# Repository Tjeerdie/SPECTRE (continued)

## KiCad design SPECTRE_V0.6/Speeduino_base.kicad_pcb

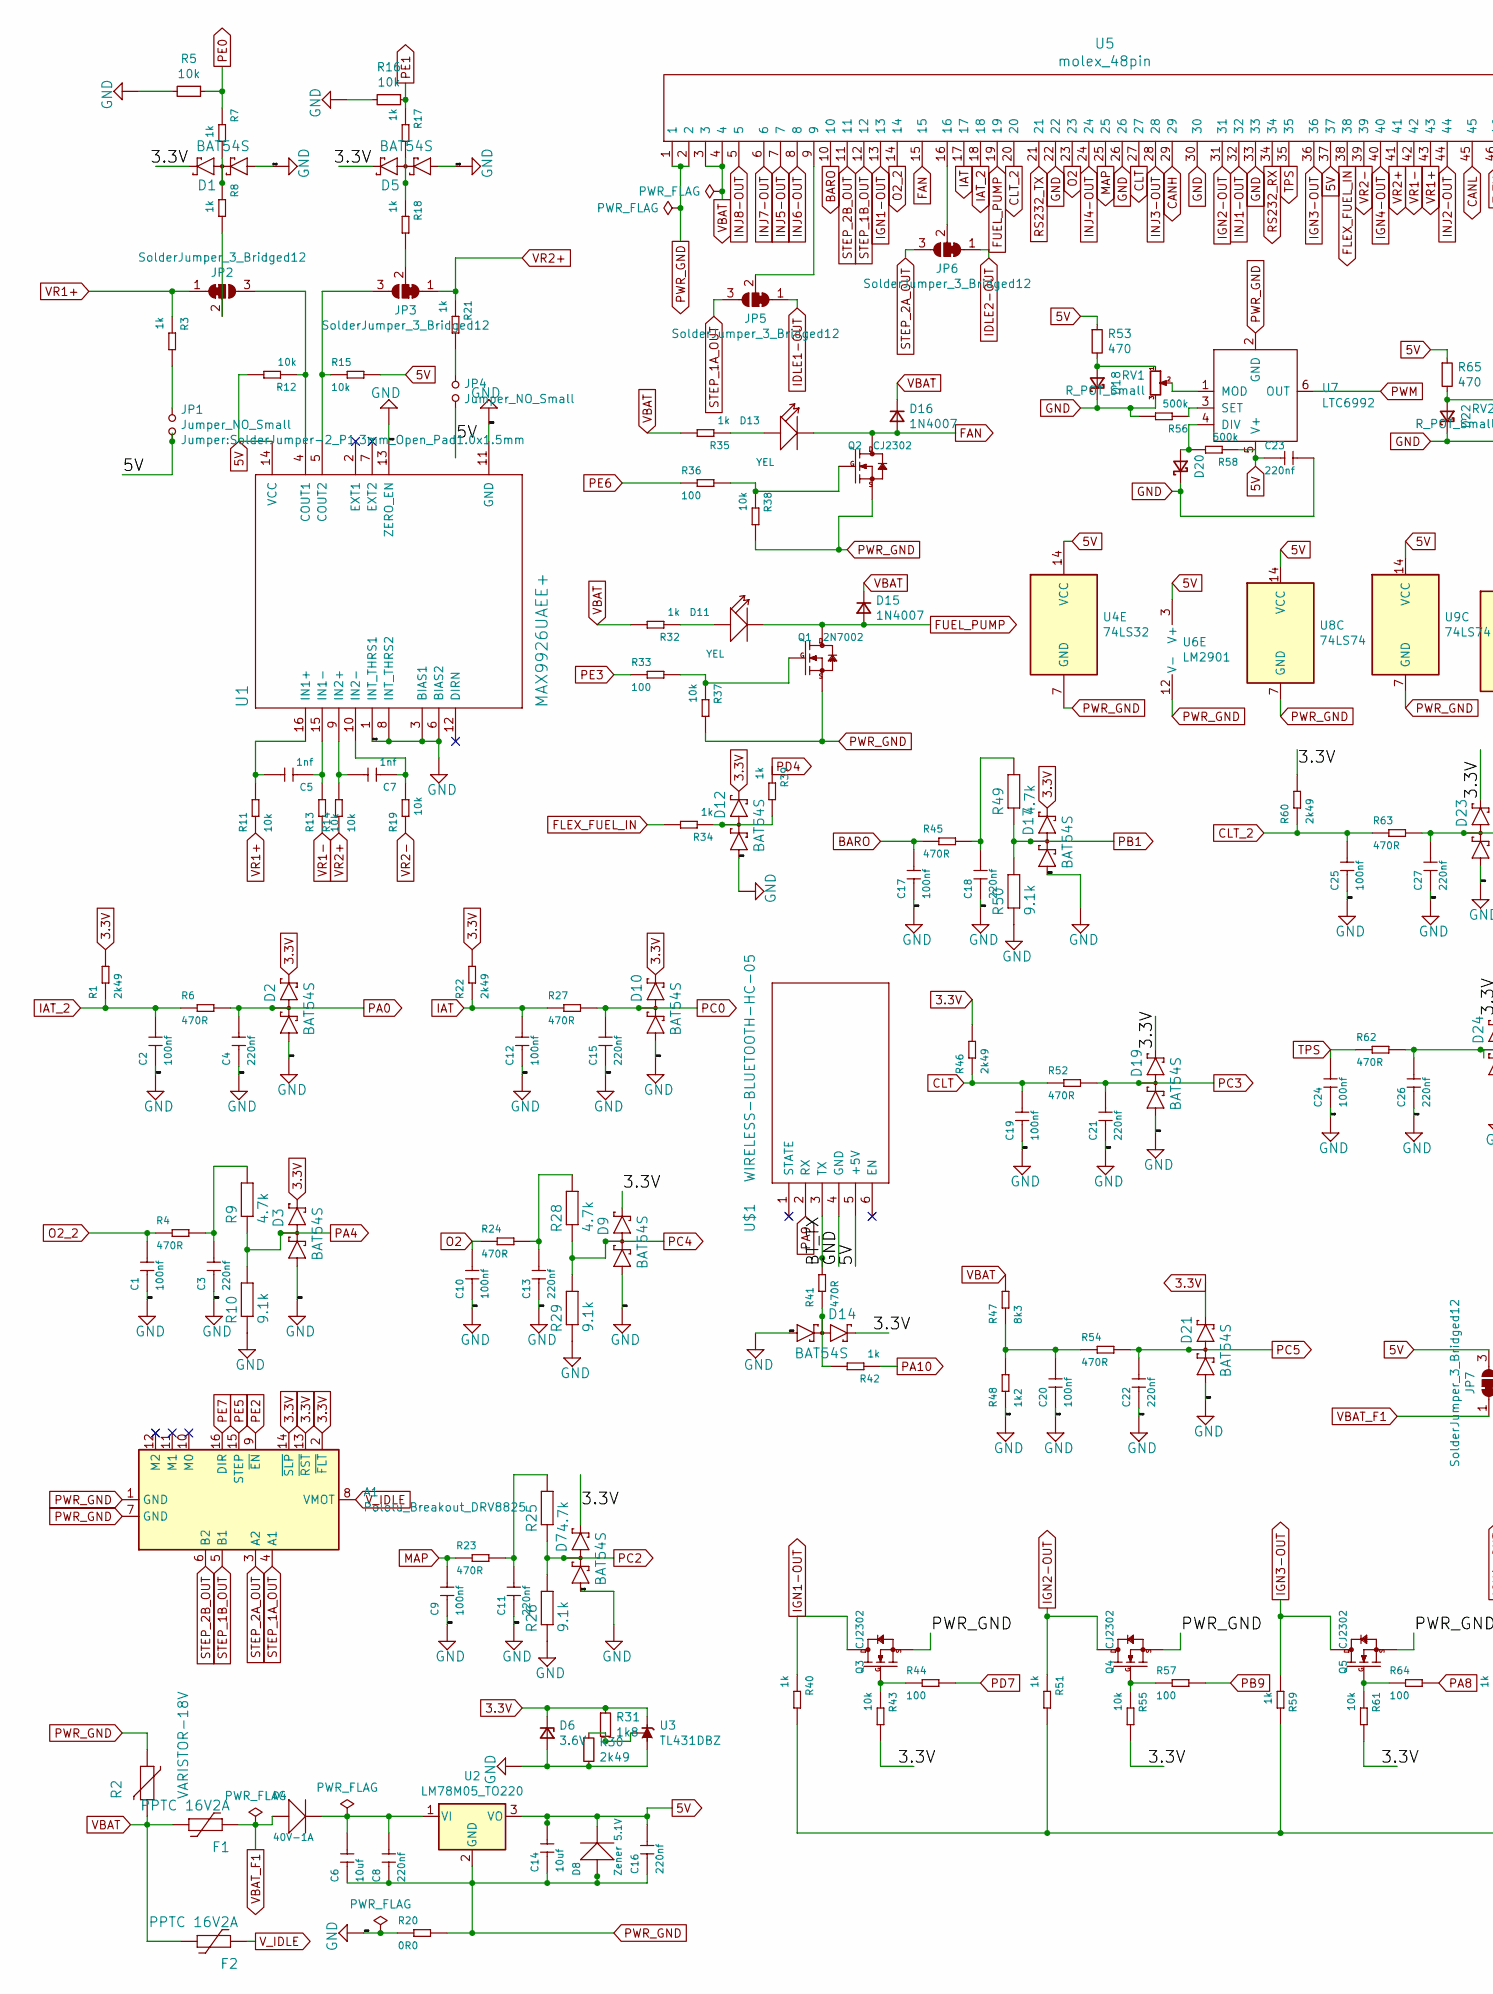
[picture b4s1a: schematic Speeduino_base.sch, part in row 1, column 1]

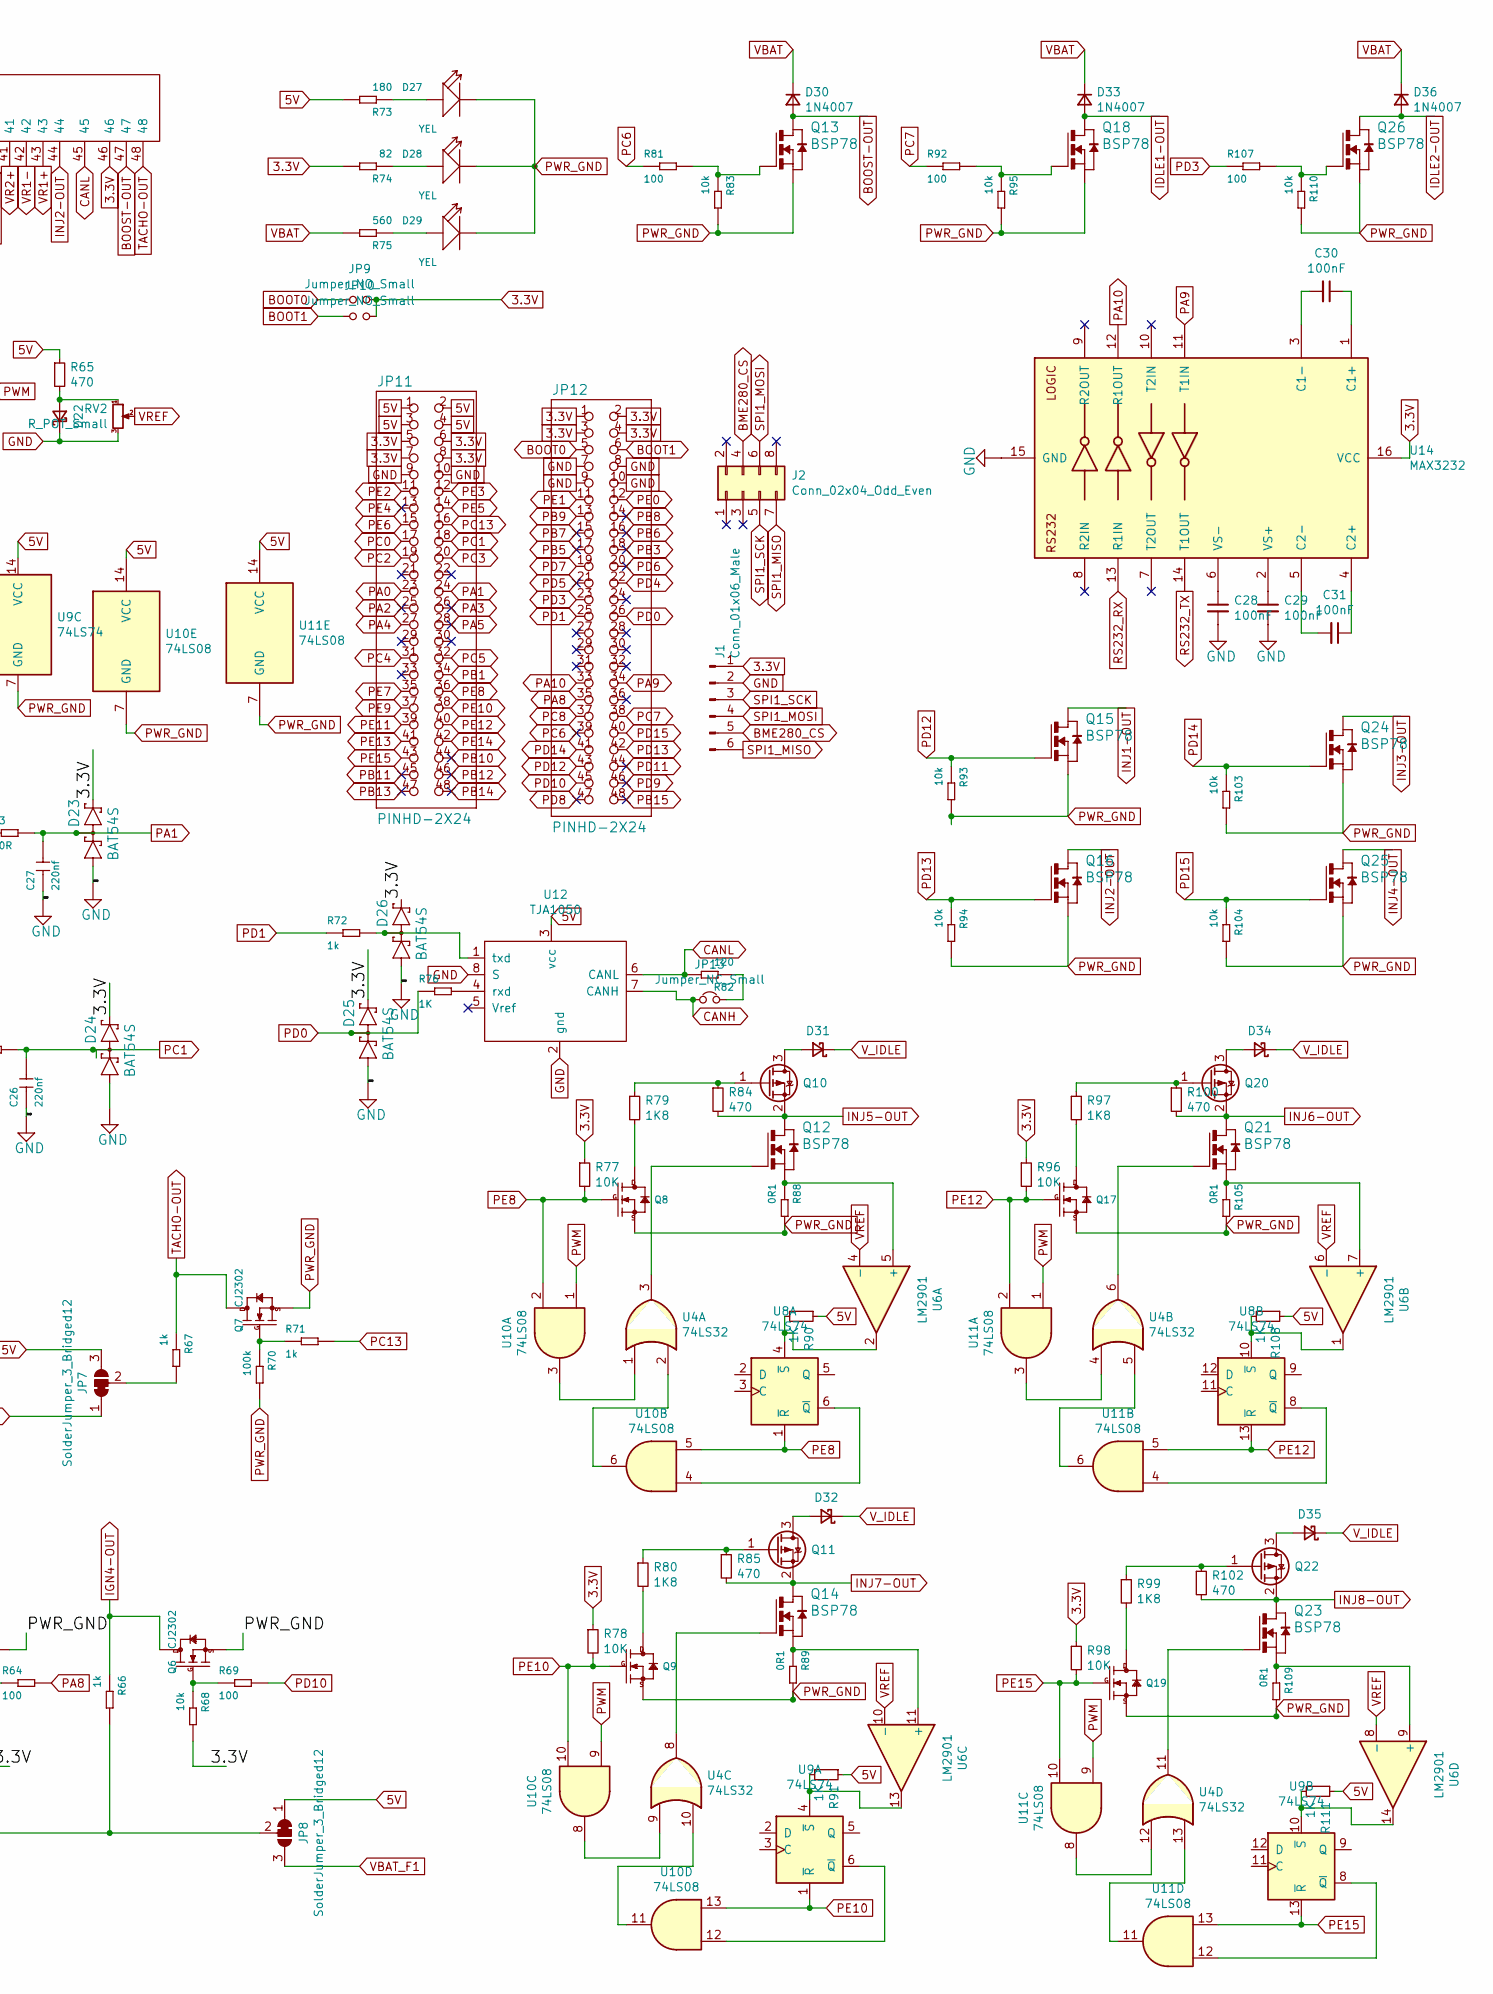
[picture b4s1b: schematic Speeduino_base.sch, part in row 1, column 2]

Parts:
A1: Pololu_Breakout_DRV8825; Pololu_Breakout-16_15.2x20.3mm
C1, C2, C9, C10, C12, C17, C19, C20, C24, C25: 100nf; C0603
C3, C4, C8, C11, C13, C15, C16, C18, C21, C22, C26, C27: 220nf; C0603
C5, C7: 1nf; C0603
C6, C14: 10uf; C1206
C23: 220nf; C_0603_1608Metric_Pad1.05x0.95mm_HandSolder
C28, C29, C30, C31: 100nF; C_0603_1608Metric
D1, D2, D3, D5, D7, D9, D10, D12, D14, D17, D19, D21, D23, D24, D25, D26: BAT54S; SOT23
D4: 40V-1A; DO-214AC
D6: 3.6V; D_MiniMELF_Handsoldering
D8: Zener 5.1V; LED-1206
D11, D13, D27, D28, D29: YEL; LED-0603
D15, D16, D30, D33, D36: 1N4007; D_SOD-128
D18, D22: LL4148; D_MiniMELF
D20: SS310; D_SOD-123
D31, D32, D34, D35: SS310; D_SMA
F1, F2: PPTC 16V2A; R_1812_4532Metric_Pad1.30x3.40mm_HandSolder
J1: Conn_01x06_Male; PinHeader_1x06_P2.54mm_Vertical
J2: Conn_02x04_Odd_Even; PinHeader_2x04_P2.54mm_Vertical
JP1, JP4: Jumper_NO_Small; SolderJumper-2_P1.3mm_Open_Pad1.0x1.5mm
JP2, JP3, JP5, JP6, JP7, JP8: SolderJumper_3_Bridged12; SolderJumper-3_P1.3mm_Bridged12_Pad1.0x1.5mm
JP9, JP10: Jumper_NO_Small; PinHeader_1x02_P2.54mm_Vertical
JP11, JP12: PINHD-2X24; 2X24
JP13: Jumper_NC_Small; SolderJumper-2_P1.3mm_Bridged_Pad1.0x1.5mm
Q1: 2N7002; SOT-23
Q2, Q3, Q4, Q5, Q6, Q7: CJ2302; SOT-23
Q8, Q9, Q17, Q19: SMD-MOSFET-N-CH-55V-2.1A-AO3422(SOT-23); SOT-23_Handsoldering
Q10, Q11, Q20, Q22: AO3401A; SOT-23_Handsoldering
Q12, Q13, Q14, Q15, Q16, Q18, Q21, Q23, Q24, Q25, Q26: BSP78; SOT223
R1, R22, R46, R60: 2k49; R0603
R2: VARISTOR-18V; RV_Disc_D12mm_W3.9mm_P7.5mm
R3: 1k; R_0603_1608Metric_Pad1.05x0.95mm_HandSolder
R4, R6, R23, R24, R27, R41, R45, R52, R54, R62, R63: 470R; R0603
R5, R16: 10k; R_0603_1608Metric_Pad1.05x0.95mm_HandSolder
R7, R8, R17, R18, R21, R32, R34, R35, R39, R40, R42, R51, R59, R66, R67, R71, R72: 1k; R0603
R9, R25, R28, R49: 4.7k; R0603
R10, R26, R29, R50: 9.1k; R0603
R11, R12, R13, R14, R15, R19, R37, R38, R43, R55, R61, R68, R83, R93, R94, R95, R103, R104, R110: 10k; R0603
R20: 0R0; R_0603_1608Metric_Pad1.05x0.95mm_HandSolder
R30: 2k49; R_0603_1608Metric_Pad1.05x0.95mm_HandSolder
R31: 1k8; R_0603_1608Metric_Pad1.05x0.95mm_HandSolder
R33, R36, R44, R57, R64, R69, R81, R92, R107: 100; R0603
R47: 8k3; R0603
R48: 1k2; R0603
R53, R65, R84, R85, R100, R102: 470; R_0603_1608Metric_Pad1.05x0.95mm_HandSolder
R56, R58: 500k; R_0603_1608Metric_Pad1.05x0.95mm_HandSolder
R70: 100k; R0603
R73: 180; R0603
R74: 82; R0603
R75: 560; R0603
R76: 1K; R0603
R77, R78, R96, R98: 10K; R_0603_1608Metric_Pad1.05x0.95mm_HandSolder
R79, R80, R97, R99: 1K8; R_0603_1608Metric_Pad1.05x0.95mm_HandSolder
R82: 120; R0603
R88, R89, R105, R109: 0R1; R_2512_6332Metric_Pad1.52x3.35mm_HandSolder
R90, R91, R108, R111: 1K; R_0603_1608Metric_Pad1.05x0.95mm_HandSolder
RV1, RV2: R_POT_Small; Potentiometer_Bourns_3314R-1_Vertical_Hole
U1: MAX9926UAEE+; 21-0055H_16
U2: LM78M05_TO220; TO-220-3_Vertical
U3: TL431DBZ; SOT-23
U4: 74LS32; SO-14_5.3x10.2mm_P1.27mm
U5: molex_48pin; Molex_48
U6: LM2901; SO-14_5.3x10.2mm_P1.27mm
U7: LTC6992; SOT-23-6
U8, U9: 74LS74; SO-14_5.3x10.2mm_P1.27mm
U10, U11: 74LS08; SO-14_5.3x10.2mm_P1.27mm
U12: TJA1050; SO-8_5.3x6.2mm_P1.27mm
U14: MAX3232; SOIC-16_4.55x10.3mm_P1.27mm
U$1: WIRELESS-BLUETOOTH-HC-05

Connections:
3.3V: A1.2 (~FLT), A1.13 (~RST), A1.14 (~SLP), D1.2 (C2), D2.2 (C2), D3.2 (C2), D5.2 (C2), D6.1 (K), D7.2 (C2), D9.2 (C2), D10.2 (C2), D12.2 (C2), D14.2 (C2), D17.2 (C2), D19.2 (C2), D21.2 (C2), D23.2 (C2), D24.2 (C2), D25.2 (C2), D26.2 (C2), J1.1, JP9.2, JP10.2, JP11.5, JP11.6, JP11.7, JP11.8, JP12.1, JP12.2, JP12.3, JP12.4, R1.2, R22.2, R31.1, R43.2, R46.2, R55.2, R60.2, R61.2, R68.2, R74.2, R77.1, R78.1, R96.1, R98.1, U3.1 (K), U5.46, U14.16 (VCC)
5V: C14.2, C16.2, C23.1, D8.-, JP1.2, JP4.2, JP7.3 (B), JP8.1 (A), JP11.1, JP11.2, JP11.3, JP11.4, R12.2, R15.2, R53.1, R58.1, R65.1, R73.2, R90.1, R91.1, R108.1, R111.1, U1.14 (VCC), U2.3 (VO), U4.14 (VCC), U5.37, U6.3 (V+), U7.5 (V+), U8.14 (VCC), U9.14 (VCC), U10.14 (VCC), U11.14 (VCC), U12.3 (vcc), U$1.5 (+5V)
/BT_TX: R41.2, U$1.3 (TX)
BARO: C17.2, R45.1, U5.10
BME280_CS: J1.5, J2.4
BOOST-OUT: D30.2 (A), Q13.2 (D), Q13.4 (D), U5.47
BOOT0: JP9.1, JP12.5
BOOT1: JP10.1, JP12.6
CANH: JP13.1, U5.29, U12.7 (CANH)
CANL: R82.2, U5.45, U12.6 (CANL)
CLT: C19.2, R46.1, R52.1, U5.27
CLT_2: C25.2, R60.1, R63.1, U5.20
FAN: D13.-, D16.2 (A), Q2.3 (D), U5.15
FLEX_FUEL_IN: R34.2, U5.38
FUEL_PUMP: D11.-, D15.2 (A), Q1.3 (D), U5.19
GND: C1.1, C2.1, C3.1, C4.1, C9.1, C10.1, C11.1, C12.1, C13.1, C15.1, C17.1, C18.1, C19.1, C20.1, C21.1, C22.1, C23.2, C24.1, C25.1, C26.1, C27.1, C28.2, C29.2, D1.1 (A1), D2.1 (A1), D3.1 (A1), D5.1 (A1), D6.2 (A), D7.1 (A1), D9.1 (A1), D10.1 (A1), D12.1 (A1), D14.1 (A1), D17.1 (A1), D18.1 (K), D19.1 (A1), D20.1 (K), D21.1 (A1), D22.1 (K), D23.1 (A1), D24.1 (A1), D25.1 (A1), D26.1 (A1), J1.2, JP11.9, JP11.10, JP12.7, JP12.8, JP12.9, JP12.10, R5.2, R10.1, R16.2, R20.1, R26.1, R29.1, R30.2, R48.1, R50.1, R56.2, RV1.3, RV2.3, U1.1 (INT_THRS1), U1.3 (BIAS1), U1.6 (BIAS2), U1.8 (INT_THRS2), U1.11 (GND), U1.13 (ZERO_EN), U3.3 (A), U5.22, U5.26, U5.30, U5.33, U12.2 (gnd), U12.8 (S), U14.15 (GND), U$1.4 (GND)
IAT: C12.2, R22.1, R27.1, U5.17
IAT_2: C2.2, R1.1, R6.1, U5.18
IDLE1-OUT: D33.2 (A), JP5.1 (A), Q18.2 (D), Q18.4 (D)
IDLE2-OUT: D36.2 (A), JP6.1 (A), Q26.2 (D), Q26.4 (D)
IGN1-OUT: Q3.3 (D), R40.1, U5.13
IGN2-OUT: Q4.3 (D), R51.1, U5.31
IGN3-OUT: Q5.3 (D), R59.1, U5.36
IGN4-OUT: Q6.3 (D), R66.1, U5.40
INJ1-OUT: Q15.2 (D), Q15.4 (D), U5.32
INJ2-OUT: Q16.2 (D), Q16.4 (D), U5.44
INJ3-OUT: Q24.2 (D), Q24.4 (D), U5.28
INJ4-OUT: Q25.2 (D), Q25.4 (D), U5.24
INJ5-OUT: Q10.2 (S), Q12.2 (D), Q12.4 (D), R84.2, U5.7
INJ6-OUT: Q20.2 (S), Q21.2 (D), Q21.4 (D), R100.2, U5.8
INJ7-OUT: Q11.2 (S), Q14.2 (D), Q14.4 (D), R85.2, U5.6
INJ8-OUT: Q22.2 (S), Q23.2 (D), Q23.4 (D), R102.2, U5.5
MAP: C9.2, R23.1, U5.25
unnamed: C3.2, R4.2, R9.2
unnamed: C5.1, R13.2, U1.15 (IN1-)
unnamed: C5.2, R11.2, U1.16 (IN1+)
unnamed: C6.2, C8.2, D4.2 (-), U2.1 (VI)
unnamed: C7.1, R19.2, U1.10 (IN2-)
unnamed: C7.2, R14.2, U1.9 (IN2+)
unnamed: C11.2, R23.2, R25.2
unnamed: C13.2, R24.2, R28.2
unnamed: C18.2, R45.2, R49.2
unnamed: C20.2, R47.1, R48.2, R54.1
unnamed: C28.1, U14.6 (VS-)
unnamed: C29.1, U14.2 (VS+)
unnamed: C30.1, U14.1 (C1+)
unnamed: C30.2, U14.3 (C1-)
unnamed: C31.1, U14.4 (C2+)
unnamed: C31.2, U14.5 (C2-)
unnamed: D1.3 (C1A2), R7.2, R8.1
unnamed: D5.3 (C1A2), R17.2, R18.1
unnamed: D11.+, R32.1
unnamed: D12.3 (C1A2), R34.1, R39.2
unnamed: D13.+, R35.1
unnamed: D14.3 (C1A2), R41.1, R42.2
unnamed: D18.2 (A), R53.2, RV1.1
unnamed: D20.2 (A), R58.2, U7.4 (DIV)
unnamed: D22.2 (A), R65.2, RV2.1
unnamed: D26.3 (C1A2), R72.2, U12.1 (txd)
unnamed: D27.+, R73.1
unnamed: D28.+, R74.1
unnamed: D29.+, R75.1
unnamed: D31.2 (A), Q10.3 (D)
unnamed: D32.2 (A), Q11.3 (D)
unnamed: D34.2 (A), Q20.3 (D)
unnamed: D35.2 (A), Q22.3 (D)
unnamed: JP1.1, R3.2
unnamed: JP2.2 (C), R8.2
unnamed: JP2.3 (B), R12.1, U1.4 (COUT1)
unnamed: JP3.2 (C), R18.2
unnamed: JP3.3 (B), R15.1, U1.5 (COUT2)
unnamed: JP4.1, R21.2
unnamed: JP5.2 (C), U5.9
unnamed: JP6.2 (C), U5.16
unnamed: JP7.2 (C), R67.2
unnamed: JP8.2 (C), R40.2, R51.2, R59.2, R66.2
unnamed: JP13.2, R82.1
unnamed: Q1.1 (G), R33.2, R37.1
unnamed: Q2.1 (G), R36.2, R38.1
unnamed: Q3.1 (G), R43.1, R44.1
unnamed: Q4.1 (G), R55.1, R57.1
unnamed: Q5.1 (G), R61.1, R64.1
unnamed: Q6.1 (G), R68.1, R69.1
unnamed: Q7.1 (G), R70.1, R71.1
unnamed: Q8.3 (D), R79.2
unnamed: Q9.3 (D), R80.2
unnamed: Q10.1 (G), R79.1, R84.1
unnamed: Q11.1 (G), R80.1, R85.1
unnamed: Q12.1 (G), U4.3
unnamed: Q12.3 (S), R88.1, U6.5 (+)
unnamed: Q13.1 (G), R81.2, R83.1
unnamed: Q14.1 (G), U4.8
unnamed: Q14.3 (S), R89.1, U6.11 (+)
unnamed: Q17.3 (D), R97.2
unnamed: Q18.1 (G), R92.2, R95.1
unnamed: Q19.3 (D), R99.2
unnamed: Q20.1 (G), R97.1, R100.1
unnamed: Q21.1 (G), U4.6
unnamed: Q21.3 (S), R105.1, U6.7 (+)
unnamed: Q22.1 (G), R99.1, R102.1
unnamed: Q23.1 (G), U4.11
unnamed: Q23.3 (S), R109.1, U6.9 (+)
unnamed: Q26.1 (G), R107.2, R110.1
unnamed: R30.1, R31.2, U3.2 (REF)
unnamed: R56.1, U7.3 (SET)
unnamed: R76.2, U12.4 (rxd)
unnamed: R90.2, U6.2, U8.4 (~S)
unnamed: R91.2, U6.13, U9.4 (~S)
unnamed: R108.2, U6.1, U8.10 (~S)
unnamed: R111.2, U6.14, U9.10 (~S)
unnamed: RV1.2, U7.1 (MOD)
unnamed: U4.1, U10.3
unnamed: U8.6 (~Q), U10.4
unnamed: U4.2, U10.6
unnamed: U4.9, U10.8
unnamed: U4.10, U10.11
unnamed: U9.6 (~Q), U10.12
unnamed: U4.4, U11.3
unnamed: U8.8 (~Q), U11.4
unnamed: U4.5, U11.6
unnamed: U4.12, U11.8
unnamed: U4.13, U11.11
unnamed: U9.8 (~Q), U11.12
O2: C10.2, R24.1, U5.23
O2_2: C1.2, R4.1, U5.14
PA0: C4.2, D2.3 (C1A2), JP11.23, R6.2
PA1: C27.2, D23.3 (C1A2), JP11.24, R63.2
PA2: JP11.25
PA3: JP11.26
PA4: D3.3 (C1A2), JP11.27, R9.1, R10.2
PA5: JP11.28
PA8: JP12.35, R64.2
PA9: JP12.34, U14.11 (T1IN), U$1.2 (RX)
PA10: JP12.33, R42.1, U14.12 (R1OUT)
PB1: D17.3 (C1A2), JP11.34, R49.1, R50.2
PB3: JP12.18
PB5: JP12.17
PB6: JP12.16
PB7: JP12.15
PB8: JP12.14
PB9: JP12.13, R57.2
PB10: JP11.44
PB11: JP11.45
PB12: JP11.46
PB13: JP11.47
PB14: JP11.48
PB15: JP12.48
PC0: C15.2, D10.3 (C1A2), JP11.17, R27.2
PC1: C26.2, D24.3 (C1A2), JP11.18, R62.2
PC2: D7.3 (C1A2), JP11.19, R25.1, R26.2
PC3: C21.2, D19.3 (C1A2), JP11.20, R52.2
PC4: D9.3 (C1A2), JP11.31, R28.1, R29.2
PC5: C22.2, D21.3 (C1A2), JP11.32, R54.2
PC6: JP12.39, R81.1
PC7: JP12.38, R92.1
PC8: JP12.37
PC13: JP11.16, R71.2
PD0: D25.3 (C1A2), JP12.26, R76.1
PD1: JP12.25, R72.1
PD3: JP12.23, R107.1
PD4: JP12.22, R39.1
PD5: JP12.21
PD6: JP12.20
PD7: JP12.19, R44.2
PD8: JP12.47
PD9: JP12.46
PD10: JP12.45, R69.2
PD11: JP12.44
PD12: JP12.43, Q15.1 (G), R93.1
PD13: JP12.42, Q16.1 (G), R94.1
PD14: JP12.41, Q24.1 (G), R103.1
PD15: JP12.40, Q25.1 (G), R104.1
PE0: JP12.12, R5.1, R7.1
PE1: JP12.11, R16.1, R17.1
PE2: A1.9 (~EN), JP11.11
PE3: JP11.12, R33.1
PE4: JP11.13
PE5: A1.15 (STEP), JP11.14
PE6: JP11.15, R36.1
PE7: A1.16 (DIR), JP11.35
PE8: JP11.36, Q8.1 (G), R77.2, U8.1 (~R), U10.2, U10.5
PE9: JP11.37
PE10: JP11.38, Q9.1 (G), R78.2, U9.1 (~R), U10.10, U10.13
PE11: JP11.39
PE12: JP11.40, Q17.1 (G), R96.2, U8.13 (~R), U11.2, U11.5
PE13: JP11.41
PE14: JP11.42
PE15: JP11.43, Q19.1 (G), R98.2, U9.13 (~R), U11.10, U11.13
PWM: U7.6 (OUT), U10.1, U10.9, U11.1, U11.9
PWR_GND: A1.1 (GND), A1.7 (GND), C6.1, C8.1, C14.1, C16.1, D8.+, D27.-, D28.-, D29.-, Q1.2 (S), Q2.2 (S), Q3.2 (S), Q4.2 (S), Q5.2 (S), Q6.2 (S), Q7.2 (S), Q8.2 (S), Q9.2 (S), Q13.3 (S), Q15.3 (S), Q16.3 (S), Q17.2 (S), Q18.3 (S), Q19.2 (S), Q24.3 (S), Q25.3 (S), Q26.3 (S), R2.1, R20.2, R37.2, R38.2, R70.2, R83.2, R88.2, R89.2, R93.2, R94.2, R95.2, R103.2, R104.2, R105.2, R109.2, R110.2, U2.2 (GND), U4.7 (GND), U5.1, U5.2, U6.12 (V-), U7.2 (GND), U8.7 (GND), U9.7 (GND), U10.7 (GND), U11.7 (GND)
RS232_RX: U5.34, U14.13 (R1IN)
RS232_TX: U5.21, U14.14 (T1OUT)
SPI1_MISO: J1.6, J2.7
SPI1_MOSI: J1.4, J2.6
SPI1_SCK: J1.3, J2.5
STEP_1A_OUT: A1.4 (A1), JP5.3 (B)
STEP_1B_OUT: A1.5 (B1), U5.12
STEP_2A_OUT: A1.3 (A2), JP6.3 (B)
STEP_2B_OUT: A1.6 (B2), U5.11
TACHO-OUT: Q7.3 (D), R67.1, U5.48
TPS: C24.2, R62.1, U5.35
VBAT: D15.1 (K), D16.1 (K), D30.1 (K), D33.1 (K), D36.1 (K), F1.1, F2.1, R2.2, R32.2, R35.2, R47.2, R75.2, U5.3, U5.4
VBAT_F1: D4.1 (+), F1.2, JP7.1 (A), JP8.3 (B)
VR1+: JP2.1 (A), R3.1, R11.1, U5.43
VR1-: R13.1, U5.42
VR2+: JP3.1 (A), R14.1, R21.1, U5.41
VR2-: R19.1, U5.39
VREF: RV2.2, U6.4 (-), U6.6 (-), U6.8 (-), U6.10 (-)
V_IDLE: A1.8 (VMOT), D31.1 (K), D32.1 (K), D34.1 (K), D35.1 (K), F2.2

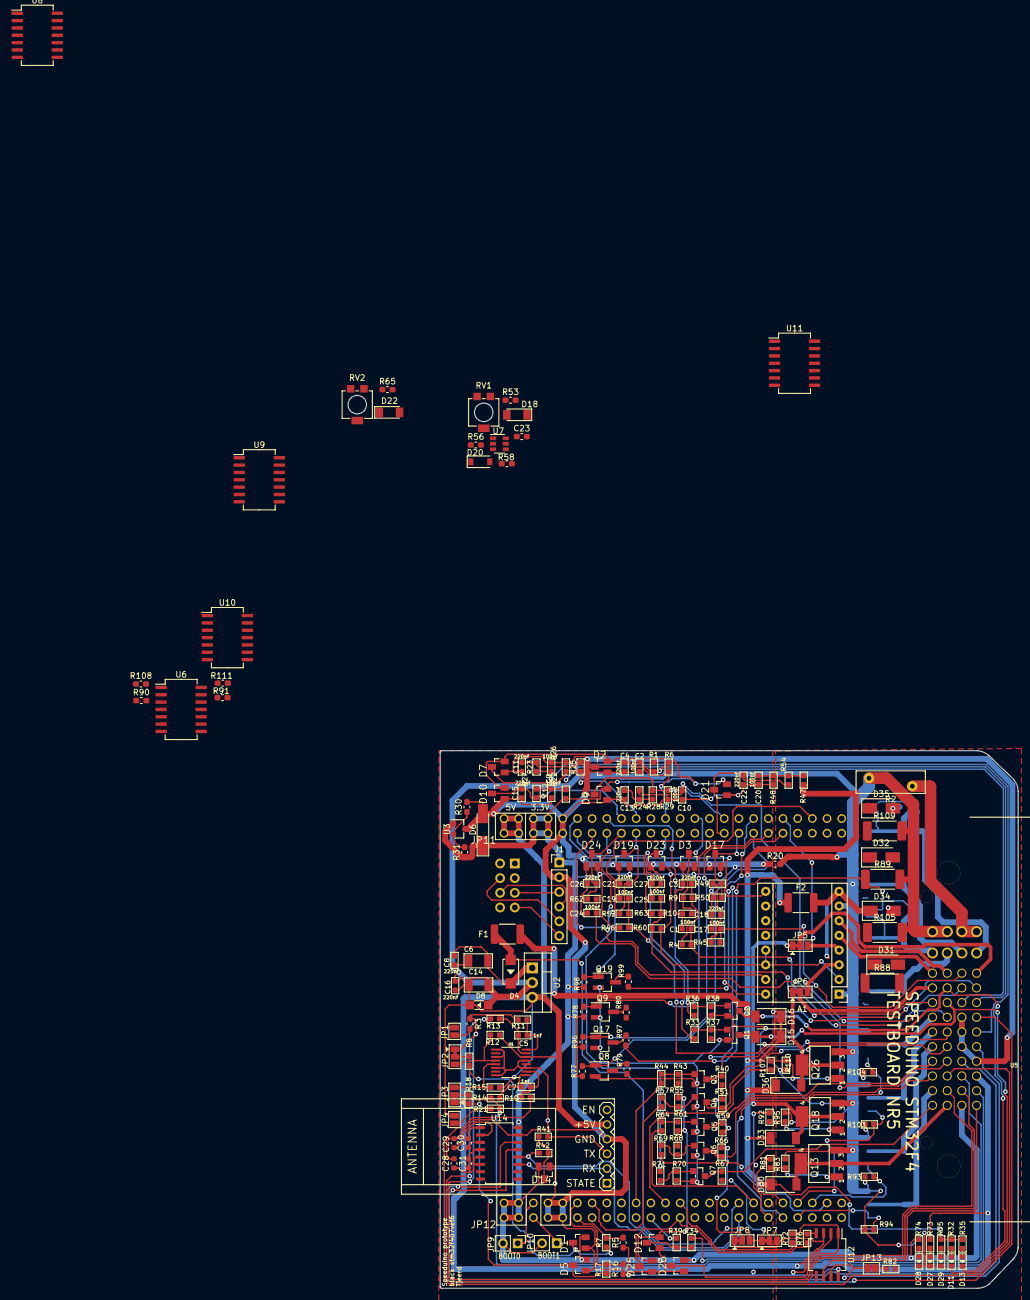
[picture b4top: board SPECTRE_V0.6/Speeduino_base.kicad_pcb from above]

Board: 2 copper layers, 100.0 x 93.0 mm, 234 parts (0 on the bottom side), 184 nets.

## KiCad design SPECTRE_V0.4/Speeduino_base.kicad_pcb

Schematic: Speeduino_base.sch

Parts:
A1: Pololu_Breakout_DRV8825; Pololu_Breakout-16_15.2x20.3mm
C1, C2, C7, C8, C11, C12, C17, C20, C21, C25: 100nf; C0603
C3, C4, C9, C10, C13, C15, C16, C19, C22, C23, C24, C26: 220nf; C0603
C5, C6: 1nf; C0603
C14, C18: 10uf; C1206
C27, C28, C29, C30: 100nF; C_0603_1608Metric
D1, D2, D3, D4, D5, D6, D7, D8, D11, D12, D14, D15, D16, D18, D28, D29: BAT54S; SOT23
D9, D17, D19, D20, D21: YEL; LED-0603
D10: 40V-1A; DO-214AC
D13: Zener 5.1V; LED-1206
D22, D23, D24, D25, D26: 1N4007; D_SOD-128
D27: 3.6V; D_MiniMELF_Handsoldering
F1, F2: PPTC 16V2A; R_1812_4532Metric_Pad1.30x3.40mm_HandSolder
J1: Conn_01x04_Male; PinHeader_1x04_P2.00mm_Vertical_SMD_Pin1Left
J2: Conn_02x04_Odd_Even; PinHeader_2x04_P2.54mm_Vertical
J3: Conn_01x06_Male; PinHeader_1x06_P2.54mm_Vertical
JP1, JP3: PINHD-2X24; 2X24
JP2, JP4, JP9, JP10, JP11, JP12: SolderJumper_3_Bridged12; SolderJumper-3_P1.3mm_Bridged12_Pad1.0x1.5mm
JP13, JP14: Jumper_NO_Small; SolderJumper-2_P1.3mm_Open_Pad1.0x1.5mm
JP16, JP17: Jumper_NO_Small; PinHeader_1x02_P2.54mm_Vertical
Q1: 2N7002; SOT-23
Q2, Q3, Q4, Q7, Q8, Q9: CJ2302; SOT-23
Q5, Q6, Q10, Q11, Q12, Q13, Q14, Q15, Q16, Q17, Q18: BSP78; SOT223
R1, R15, R28, R34: 2k49; R0603
R2: 1k; R_0603_1608Metric_Pad1.05x0.95mm_HandSolder
R3, R5, R17, R18, R24, R32, R33, R35, R38, R39, R66: 470R; R0603
R4, R13, R16, R21, R22, R25, R26, R40, R43, R45, R46, R51, R54, R57, R73, R74, R83: 1k; R0603
R6, R9, R10, R11, R12, R14, R29, R41, R47, R48, R49, R52, R56, R60, R61, R62, R63, R64, R78, R79, R80, R81, R82: 10k; R0603
R7, R19, R36, R67: 4.7k; R0603
R8, R20, R37, R68: 9.1k; R0603
R23: VARISTOR-18V; RV_Disc_D12mm_W3.9mm_P7.5mm
R27, R42, R50, R53, R55, R58, R59, R65, R77: 100; R0603
R30: 8k3; R0603
R31: 1k2; R0603
R44: 100k; R0603
R69: 180; R0603
R70: 82; R0603
R71: 560; R0603
R72: 0R0; R_0603_1608Metric_Pad1.05x0.95mm_HandSolder
R75, R76: 10k; R_0603_1608Metric_Pad1.05x0.95mm_HandSolder
R84: 1K; R0603
U1: MAX9926UAEE+; 21-0055H_16
U2: molex_48pin; Molex_48
U3: LM78M05_TO220; TO-220-3_Vertical
U4: MAX3232; SOIC-16_4.55x10.3mm_P1.27mm
U$2: WIRELESS-BLUETOOTH-HC-05
U?1: TJA1050; SO-8_5.3x6.2mm_P1.27mm

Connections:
3.3V: A1.2 (~FLT), A1.13 (~RST), A1.14 (~SLP), D1.2 (C2), D2.2 (C2), D3.2 (C2), D4.2 (C2), D5.2 (C2), D6.2 (C2), D7.2 (C2), D8.2 (C2), D11.2 (C2), D12.2 (C2), D14.2 (C2), D15.2 (C2), D16.2 (C2), D18.2 (C2), D27.1 (K), D28.2 (C2), D29.2 (C2), J1.1, J3.1, JP1.5, JP1.6, JP1.7, JP1.8, JP3.1, JP3.2, JP3.3, JP3.4, JP16.2, JP17.2, R1.2, R15.2, R28.2, R34.2, R41.2, R47.2, R52.2, R60.2, R70.2, U2.46, U4.16
5V: C18.2, C22.2, D13.-, JP1.1, JP1.2, JP1.3, JP1.4, JP2.3 (B), JP4.1 (A), JP13.2, JP14.2, R9.2, R12.2, R69.2, U1.14 (VCC), U2.37, U3.3 (VO), U$2.5 (+5V), U?1.3 (vcc)
/BT_TX: R24.2, U$2.3 (TX)
BARO: C25.2, R66.1, U2.10
BME280_CS: J2.4, J3.5
BOOST-OUT: D26.2 (A), Q14.2 (D), Q14.4 (D), U2.47
BOOT0: JP3.5, JP16.1
BOOT1: JP3.6, JP17.1
CANH: U2.43, U?1.7 (CANH)
CANL: U2.45, U?1.6 (CANL)
CLT: C11.2, R28.1, R32.1, U2.31
CLT_2: C20.2, R34.1, R38.1, U2.21
FAN: D17.-, D23.2 (A), Q9.3 (D), U2.15
FLEX_FUEL_IN: R21.2, U2.38
FUEL_PUMP: D9.-, D22.2 (A), Q1.3 (D), U2.17
GND: C1.1, C2.1, C3.1, C4.1, C7.1, C8.1, C9.1, C10.1, C11.1, C12.1, C13.1, C15.1, C17.1, C19.1, C20.1, C21.1, C23.1, C24.1, C25.1, C26.1, C27.2, C28.2, D1.1 (A1), D2.1 (A1), D3.1 (A1), D4.1 (A1), D5.1 (A1), D6.1 (A1), D7.1 (A1), D8.1 (A1), D11.1 (A1), D12.1 (A1), D14.1 (A1), D15.1 (A1), D16.1 (A1), D18.1 (A1), D27.2 (A), D28.1 (A1), D29.1 (A1), J1.4, J3.2, JP1.9, JP1.10, JP3.7, JP3.8, JP3.9, JP3.10, R8.1, R20.1, R31.1, R37.1, R68.1, R72.1, R75.2, R76.2, U1.1 (INT_THRS1), U1.3 (BIAS1), U1.6 (BIAS2), U1.8 (INT_THRS2), U1.11 (GND), U1.13 (ZERO_EN), U2.22, U2.26, U2.30, U2.33, U4.15, U$2.4 (GND), U?1.2 (gnd), U?1.8 (S)
IAT: C8.2, R15.1, R18.1, U2.35
IAT_2: C2.2, R1.1, R5.1, U2.42
IDLE1-OUT: D24.2 (A), JP10.1 (A), Q11.2 (D), Q11.4 (D)
IDLE2-OUT: D25.2 (A), JP9.1 (A), Q10.2 (D), Q10.4 (D)
IGN1-OUT: Q2.3 (D), R40.1, U2.13
IGN2-OUT: Q4.3 (D), R45.1, U2.36
IGN3-OUT: Q7.3 (D), R51.1, U2.40
IGN4-OUT: Q8.3 (D), R57.1, U2.16
INJ1-OUT: Q5.2 (D), Q5.4 (D), U2.32
INJ2-OUT: Q6.2 (D), Q6.4 (D), U2.44
INJ3-OUT: Q12.2 (D), Q12.4 (D), U2.28
INJ4-OUT: Q13.2 (D), Q13.4 (D), U2.24
INJ5-OUT: Q15.2 (D), Q15.4 (D), U2.7
INJ6-OUT: Q17.2 (D), Q17.4 (D), U2.8
INJ7-OUT: Q16.2 (D), Q16.4 (D), U2.6
INJ8-OUT: Q18.2 (D), Q18.4 (D), U2.5
MAP: C17.2, R35.1, U2.39
unnamed: C3.2, R3.2, R7.2
unnamed: C5.1, R10.2, U1.15 (IN1-)
unnamed: C5.2, R6.2, U1.16 (IN1+)
unnamed: C6.1, R14.2, U1.10 (IN2-)
unnamed: C6.2, R11.2, U1.9 (IN2+)
unnamed: C9.2, R17.2, R19.2
unnamed: C12.2, R30.1, R31.2, R33.1
unnamed: C14.2, C16.2, D10.2 (-), U3.1 (VI)
unnamed: C19.2, R35.2, R36.2
unnamed: C26.2, R66.2, R67.2
unnamed: C27.1, U4.6
unnamed: C28.1, U4.2
unnamed: C29.1, U4.1
unnamed: C29.2, U4.3
unnamed: C30.1, U4.4
unnamed: C30.2, U4.5
unnamed: D1.3 (C1A2), R4.2, R73.1
unnamed: D4.3 (C1A2), R13.2, R74.1
unnamed: D7.3 (C1A2), R21.1, R22.2
unnamed: D8.3 (C1A2), R24.1, R25.2
unnamed: D9.+, R26.1
unnamed: D17.+, R54.1
unnamed: D19.+, R69.1
unnamed: D20.+, R70.1
unnamed: D21.+, R71.1
unnamed: D29.3 (C1A2), R83.2, U?1.1 (txd)
unnamed: JP2.2 (C), R43.2
unnamed: JP4.2 (C), R40.2, R45.2, R51.2, R57.2
unnamed: JP9.2 (C), U2.20
unnamed: JP10.2 (C), U2.9
unnamed: JP11.2 (C), R73.2
unnamed: JP11.3 (B), R9.1, U1.4 (COUT1)
unnamed: JP12.2 (C), R74.2
unnamed: JP12.3 (B), R12.1, U1.5 (COUT2)
unnamed: JP13.1, R2.2
unnamed: JP14.1, R16.2
unnamed: Q1.1 (G), R27.2, R29.1
unnamed: Q2.1 (G), R41.1, R42.1
unnamed: Q3.1 (G), R44.1, R46.1
unnamed: Q4.1 (G), R47.1, R50.1
unnamed: Q7.1 (G), R52.1, R53.1
unnamed: Q8.1 (G), R60.1, R65.1
unnamed: Q9.1 (G), R55.2, R56.1
unnamed: Q10.1 (G), R58.2, R61.1
unnamed: Q11.1 (G), R59.2, R62.1
unnamed: Q14.1 (G), R77.2, R78.1
unnamed: R84.2, U?1.4 (rxd)
O2: C7.2, R17.1, U2.27
O2_2: C1.2, R3.1, U2.41
PA0: JP1.23
PA1: C23.2, D15.3 (C1A2), JP1.24, R38.2
PA2: C4.2, D2.3 (C1A2), JP1.25, R5.2
PA3: D3.3 (C1A2), JP1.26, R7.1, R8.2
PA4: JP1.27
PA5: JP1.28
PA8: JP3.35, R53.2
PA9: J1.3, JP3.34
PA10: J1.2, JP3.33
PB1: D18.3 (C1A2), JP1.34, R67.1, R68.2
PB3: JP3.18
PB5: JP3.17
PB6: JP3.16
PB7: JP3.15
PB8: JP3.14
PB9: JP3.13, R50.2
PB10: JP1.44
PB11: JP1.45
PB12: JP1.46
PB13: JP1.47
PB14: JP1.48
PB15: JP3.48
PC0: D14.3 (C1A2), JP1.17, R36.1, R37.2
PC1: C24.2, D16.3 (C1A2), JP1.18, R39.2
PC2: C10.2, D5.3 (C1A2), JP1.19, R18.2
PC3: C13.2, D11.3 (C1A2), JP1.20, R32.2
PC4: D6.3 (C1A2), JP1.31, R19.1, R20.2
PC5: C15.2, D12.3 (C1A2), JP1.32, R33.2
PC6: JP3.39
PC7: JP3.38, R77.1
PC8: JP3.37, R59.1
PC13: JP1.16, R46.2
PD0: D28.3 (C1A2), JP3.26, R84.1
PD1: JP3.25, R83.1
PD3: JP3.23, R58.1
PD4: JP3.22, R22.1
PD5: JP3.21
PD6: JP3.20
PD7: JP3.19, R42.2
PD8: JP3.47, U4.11, U$2.2 (RX)
PD9: JP3.46, R25.1, U4.12
PD10: JP3.45, R65.2
PD11: JP3.44
PD12: JP3.43, Q5.1 (G), R48.1
PD13: JP3.42, Q6.1 (G), R49.1
PD14: JP3.41, Q12.1 (G), R63.1
PD15: JP3.40, Q13.1 (G), R64.1
PE0: JP3.12, R4.1, R75.1
PE1: JP3.11, R13.1, R76.1
PE2: A1.9 (~EN), JP1.11
PE3: JP1.12, R27.1
PE4: JP1.13
PE5: A1.15 (STEP), JP1.14
PE6: JP1.15, R55.1
PE7: A1.16 (DIR), JP1.35
PE8: JP1.36
PE9: JP1.37
PE10: JP1.38
PE11: JP1.39, Q17.1 (G), R81.1
PE12: JP1.40, Q15.1 (G), R79.1
PE13: JP1.41, Q16.1 (G), R80.1
PE14: JP1.42, Q18.1 (G), R82.1
PE15: JP1.43
PWR_GND: A1.1 (GND), A1.7 (GND), C14.1, C16.1, C18.1, C22.1, D13.+, D19.-, D20.-, D21.-, Q1.2 (S), Q2.2 (S), Q3.2 (S), Q4.2 (S), Q5.3 (S), Q6.3 (S), Q7.2 (S), Q8.2 (S), Q9.2 (S), Q10.3 (S), Q11.3 (S), Q12.3 (S), Q13.3 (S), Q14.3 (S), Q15.3 (S), Q16.3 (S), Q17.3 (S), Q18.3 (S), R23.1, R29.2, R44.2, R48.2, R49.2, R56.2, R61.2, R62.2, R63.2, R64.2, R72.2, R78.2, R79.2, R80.2, R81.2, R82.2, U2.1, U2.2, U3.2 (GND)
RS232_RX: U2.29, U4.13
RS232_TX: U2.25, U4.14
SPI1_MISO: J2.7, J3.6
SPI1_MOSI: J2.6, J3.4
SPI1_SCK: J2.5, J3.3
STEP_1A_OUT: A1.4 (A1), JP10.3 (B)
STEP_1B_OUT: A1.5 (B1), U2.12
STEP_2A_OUT: A1.3 (A2), JP9.3 (B)
STEP_2B_OUT: A1.6 (B2), U2.11
TACHO-OUT: Q3.3 (D), R43.1, U2.48
TPS: C21.2, R39.1, U2.34
VBAT: D22.1 (K), D23.1 (K), D24.1 (K), D25.1 (K), D26.1 (K), F1.1, F2.1, R23.2, R26.2, R30.2, R54.2, R71.2, U2.3, U2.4
VBAT_F1: D10.1 (+), F1.2, JP2.1 (A), JP4.3 (B)
VR1+: JP11.1 (A), R2.1, R6.1, U2.14
VR1-: R10.1, U2.23
VR2+: JP12.1 (A), R11.1, R16.1, U2.19
VR2-: R14.1, U2.18
V_IDLE: A1.8 (VMOT), F2.2

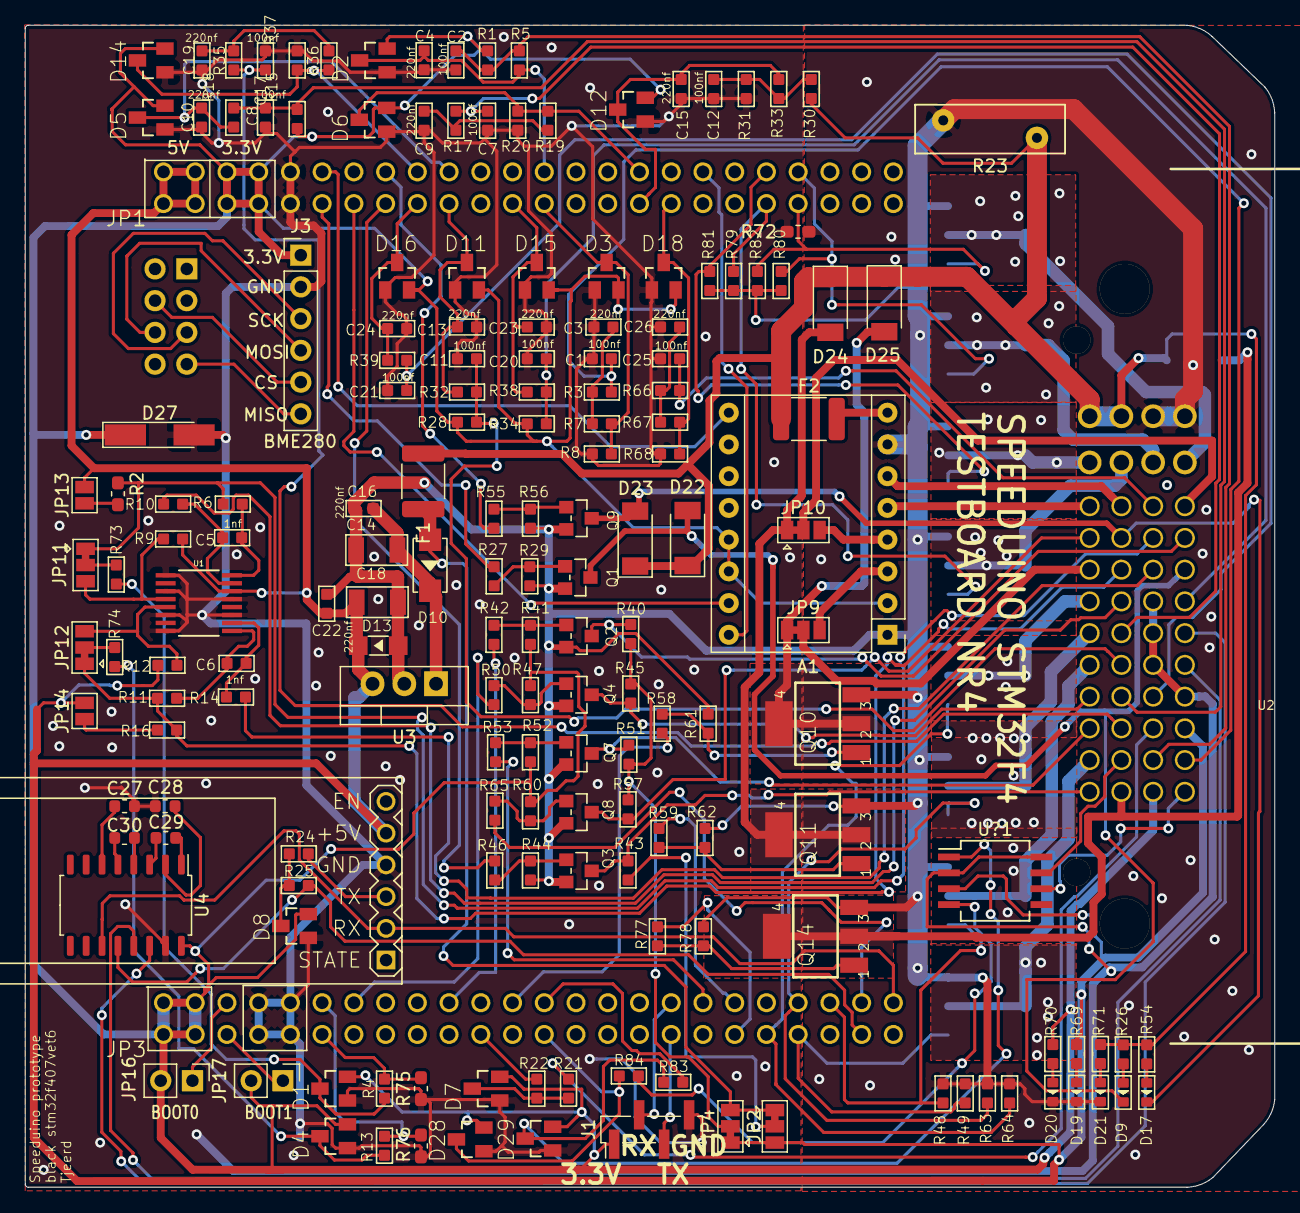
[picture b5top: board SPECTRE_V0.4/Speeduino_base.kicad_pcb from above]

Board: 2 copper layers, 100.0 x 93.0 mm, 185 parts (0 on the bottom side), 141 nets.

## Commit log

2020-02-27 Cleaned up foler 0.4
2020-02-27 Cleaned up V0.4 Bug fixes in board V0.4 Changed readme to add more to be tested functions
2020-02-27 changed some readme info
2020-03-22 Lots of changes, started new PCB with 8 inj channels.
2020-03-22 All tracks routed: TODO: Copper GND, Copper Cooling transistors, Check to220 5v direction
2020-03-23 Added copper planes
2020-03-23 Add zener for safety on 3.3v. All bat54S diodes dump current on 3.3V line when driven above 3.6V therefor the 3.3V needed protection
2020-03-25 add canbus driver add 3d models to components for 3d render.
2020-03-25 Update TODOFixes
    Updated TODIO list
2020-03-26 rs232 header NRF
    Added rs232 driver and Added NRF header to use SPI .
    TODO:
    - finish rs232 to 48 pin connector
    - route BME280
2020-03-28 rs232 + BME280 finished
    Added rs232 to connector
    Finished BME280 connection and routing
2020-03-28 Added board v0.5
    Added new board V0.5 also generetd gerbers for V0.4
2020-03-28 update silkscreen
    Updated silkscreen V0.4. Start switchable flyback diode in V0.5 for PWM control of injectors
2020-03-28 Routing V0.5
    Started routing board V0.5
2020-03-29 WPM peak&hold low-z injector driver
    Add a PWM peak and hold injector driver simulation in LTspice. Not perfect yet but good learning experience.
2020-03-31 Low-z sim update
    Update low Z injector driver simulation
2020-03-31 peak & hold injector driver update
    Updates to Low-z PWM peak & hold injector driver schematic.
    Updates simulation low-z driver.
2020-03-31 Updates on routing V0.5 board
    Switched some pins also updated the board routing a bit. not done yet.
2020-04-01 Update PWM low-z injector.asc
    Updates low-z peak and hold sim with lower resistor values
2020-04-04 Routing and testing
    Test Some more functions of the V0.3 also routed the V0.5 furhter
2020-04-05 Somem ore routing V0.5
    Routing board V0.5
2020-04-05 3.3V power protection
    Extra protection for the 3.3volt supply. TL431 is used for this.
2020-04-05 routing V0.5
    Some more routing V0.5
2020-04-05 V0.5 fully routed
    Routed the whole SPECTRE V0.5 board
2020-04-05 Updated some photos
2020-04-05 Fixed some DRC errors
2020-04-06 Added 3d renders V0.5
2020-04-07 updated gerbers
2020-04-08 Cleanedup acute angles
    Cleaned up a lot of the accute angles as suggested by JHolland on the forum
2020-04-08 updated bluetooth
    Now bluetooth is not on second serial anymore. Bluetooth is on Serial1
2020-04-10 Started on peak & hold schematic
2020-05-07 boost pin change
    update pin def boost pin
2020-07-02 Stared implementing peak and hold driver. Also started in V0.6 of my board where the peak and hold driver is included
2020-07-03 Cleaned and updated the SPECTRE V0.5 Created separate Peak and Hold board.
2020-07-03 cleanup
2020-07-03 create gerberbers
    created gerbers for the order. Peak and Hold and the SPECTRE V0.5
2020-07-13 Removed peak&hold driver from this repo. Update resistor values in schematic to values that work. Cleaned up resistor naming.
2020-07-13 update to README
2020-07-13 updates to README
2020-07-13 Removed V0.6 because there is not going to be a V0.6 anytime soon.
2020-07-19 clean-up board V0.5 started on board V0.5.1
2020-07-19 re-add bluetooth module
2020-07-19 Clean-up PCB V0.5.1
2020-07-19 Renumbered all parts from start
2020-08-01 Add V0.5.1
    Added V0.5.2
    - Proto area
    - 6ign outputs
    - mosfet drivers for ign outputs
2020-08-01 Update ign5 pin
2020-08-04 Updates on V0.5.2
2020-08-04 Update zener value
2020-11-11 Start on V0.5.3
    Started on V0.5.3 tfor some inprovements
    - Seriie resistance for ignition drivers
    - Boot0 to external connector for easy flashing when ECU is hard to reach
    - Simplify the and improve robustness of VR/HALL sensor stuff
2020-12-30 Organization
2020-12-30 Now with correct file/lib locations for the 48pin molex
2020-12-30 more cleanup after changing molex 48pin
2020-12-30 update molex 48 pin to correct location
2020-12-30 updated BOM
2021-01-18 Complete rework on PCB
2021-01-26 Increase Vbat flyback diode trackwidth
2021-01-28 cleaning up board
2021-01-28 Done re-routing
2021-01-28 Clean-up board
2021-01-28 Added V0.5.4 by Vitor_Boss
2021-01-30 docs: update README with TS mappings
2021-01-30 Update Canbus interface
2021-02-08 Update V0.5.3 Update JLCpcb part numbers in schematic Updated board layout. Added bom for JLCPCB SMT service Added location file for JLCPCB SMT service
2021-03-05 General cleanup, update Readme and add BOM list
2021-04-15 Add VSS description to read-me
2021-05-18 Update readme with jumper settings
2022-02-20 workound is no longer working
2023-12-09 add connector pinout figure
2023-12-09 Update README.MD
    adding pinout connector to readme
2023-12-09 Update README.MD
    update latest version comments in the readme
